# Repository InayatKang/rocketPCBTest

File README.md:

Practice PCB, rocket themed for measuring temperature of surroundings.
Equipped with DHT11

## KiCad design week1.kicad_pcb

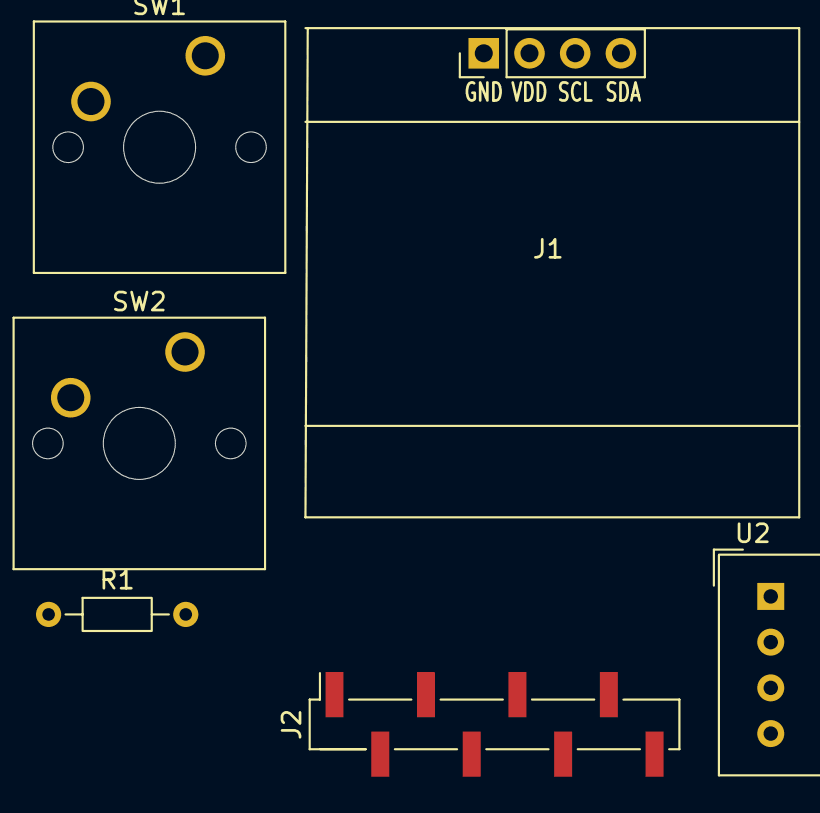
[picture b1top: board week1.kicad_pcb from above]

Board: 2 copper layers, 6 parts (0 on the bottom side), 4 nets, no tracks yet.

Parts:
J1: Conn_01x04_Pin; Display_128x64_096_I2C
J2: Conn_01x08_Pin; PinHeader_1x08_P2.54mm_Vertical_SMD_Pin1Right
R1: 10k; R_Axial_DIN0204_L3.6mm_D1.6mm_P7.62mm_Horizontal
SW1, SW2: SW_Push; SW_Cherry_MX_1.00u_PCB
U2: DHT11; Aosong_DHT11_5.5x12.0_P2.54mm

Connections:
+3.3V: J2.1, R1.1, U2.1 (VDD)
/GPIO2: J1.3, J1.4, J2.3, J2.4, SW1.1, SW2.1
GND: J2.2, SW1.2, SW2.2, U2.4 (GND)
unnamed: R1.2, U2.2 (DATA)
